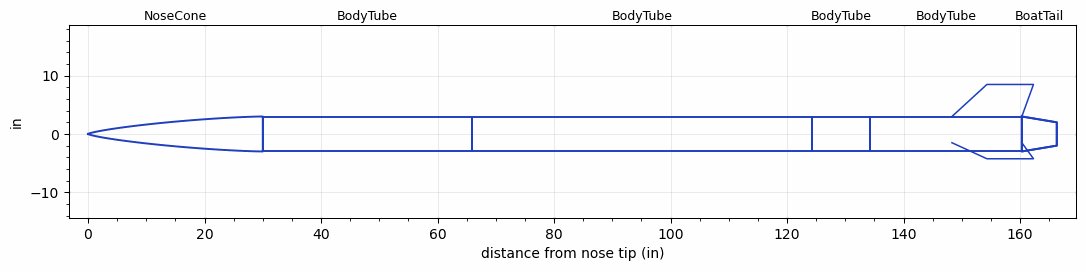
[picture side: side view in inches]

<RASAeroDocument>
 <FileVersion>2</FileVersion>
 <RocketDesign>
  <NoseCone>
   <Length>29.9999</Length>
   <Diameter>6</Diameter>
   <Shape>Von Karman Ogive</Shape>
   <Location>0</Location>
  </NoseCone>
  <BodyTube>
   <Length>35.9999</Length>
   <Diameter>6</Diameter>
   <Location>29.9999</Location>
  </BodyTube>
  <BodyTube>
   <Length>58.2999</Length>
   <Diameter>6</Diameter>
   <Location>65.9998</Location>
  </BodyTube>
  <BodyTube>
   <Length>10</Length>
   <Diameter>6</Diameter>
   <Location>124.2997</Location>
  </BodyTube>
  <BodyTube>
   <Length>25.9999</Length>
   <Diameter>6</Diameter>
   <Location>134.2997</Location>
   <BoattailLength>6</BoattailLength>
   <BoattailRearDiameter>4</BoattailRearDiameter>
   <Fin>
    <Count>3</Count>
    <Chord>12</Chord>
    <Span>5.5</Span>
    <SweepDistance>6</SweepDistance>
    <TipChord>8</TipChord>
    <Thickness>0.28</Thickness>
    <Location>12</Location>
    <AirfoilSection>Square</AirfoilSection>
   </Fin>
  </BodyTube>
  <BoatTail>
   <Length>6</Length>
   <Diameter>6</Diameter>
   <RearDiameter>4</RearDiameter>
   <Location>160.2996</Location>
  </BoatTail>
  <Surface>Rough Camouflage Paint</Surface>
  <ModifiedBarrowman>False</ModifiedBarrowman>
  <Turbulence>False</Turbulence>
  <UseBooster1>False</UseBooster1>
  <UseBooster2>False</UseBooster2>
 </RocketDesign>
 <LaunchSite>
  <Altitude>0</Altitude>
  <Pressure>29.9214</Pressure>
  <RodAngle>0</RodAngle>
  <RodLength>3.2808</RodLength>
  <Temperature>59</Temperature>
  <WindSpeed>4.4739</WindSpeed>
 </LaunchSite>
 <Recovery>
  <Altitude1>656.168</Altitude1>
  <Altitude2>656.168</Altitude2>
  <DeviceType1>Parachute</DeviceType1>
  <DeviceType2>Parachute</DeviceType2>
  <Event1>True</Event1>
  <Event2>True</Event2>
  <Size1>11.811</Size1>
  <Size2>11.811</Size2>
  <EventType1>Apogee</EventType1>
  <EventType2>Apogee</EventType2>
  <CD1>0.8</CD1>
  <CD2>0</CD2>
 </Recovery>
 <SimulationList>
  <Simulation>
   <SustainerEngine>N27-30k(THRUSTMIKEY)  (TAMUSRT-30k)</SustainerEngine>
   <SustainerLaunchWt>137.83</SustainerLaunchWt>
   <SustainerCG>102.74</SustainerCG>
   <SustainerIgnitionDelay>0</SustainerIgnitionDelay>
   <Booster1SeparationDelay>0</Booster1SeparationDelay>
   <Booster1IgnitionDelay>0</Booster1IgnitionDelay>
   <IncludeBooster1>False</IncludeBooster1>
   <Booster2Delay>0</Booster2Delay>
   <IncludeBooster2>False</IncludeBooster2>
   <TimetoApogee>45.45838</TimetoApogee>
   <MaxAltitude>31490.94</MaxAltitude>
   <MaxVelocity>1526.665</MaxVelocity>
  </Simulation>
 </SimulationList>
</RASAeroDocument>
